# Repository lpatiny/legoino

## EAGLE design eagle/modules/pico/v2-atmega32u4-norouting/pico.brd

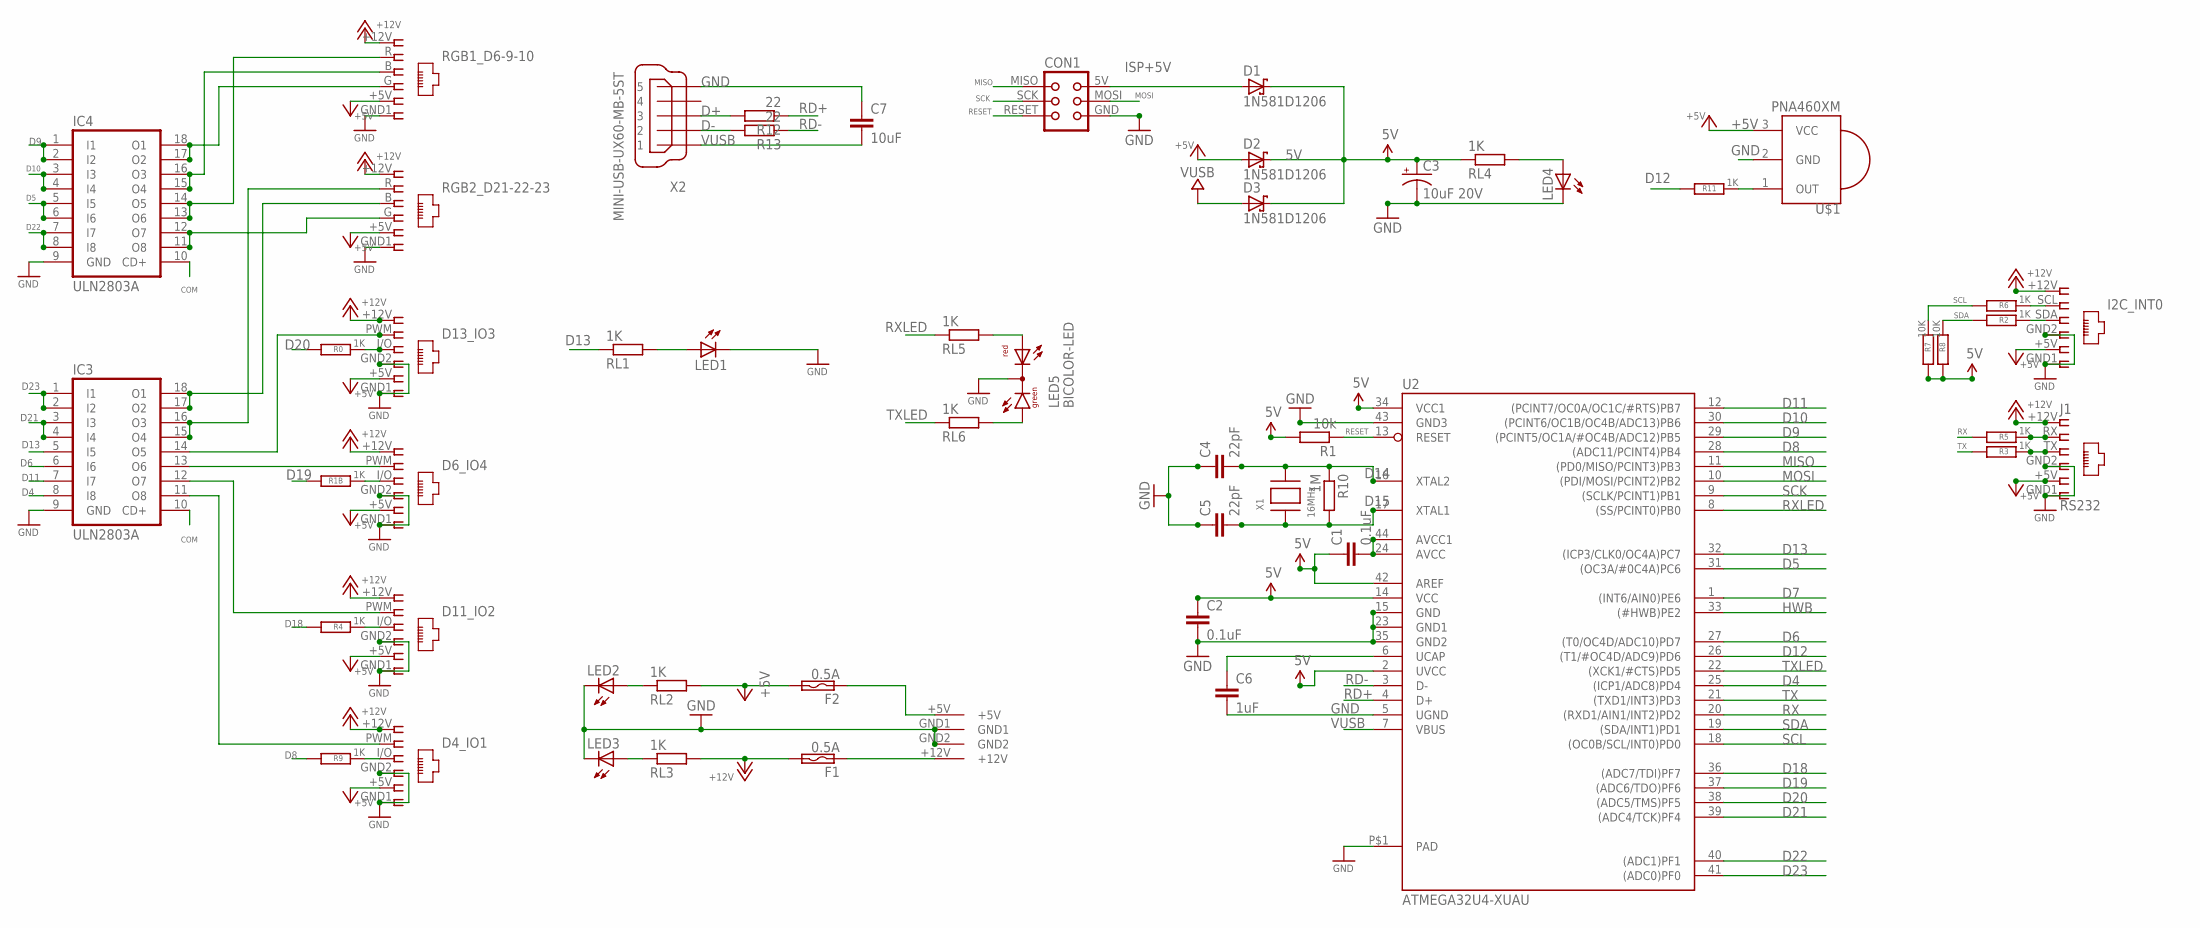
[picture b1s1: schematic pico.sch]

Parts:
C1, C2: 0.1uF; C1206
C3: 10uF 20V; EIA3216-KIT
C4, C5: 22pF; C1206
C6: 1uF; C1206
C7: 10uF; C1206
CON1: TINYISPT; TC2030-MCP-NL
D1, D2, D3: 1N581D1206; LED-1206
D4_IO1: IO1; RJ12-STRAIGHT
D6_IO4: IO3; RJ12-STRAIGHT
D11_IO2: IO2; RJ12-STRAIGHT
D13_IO3: IO4; RJ12-STRAIGHT
F1, F2: 0.5A; C1812
I2C_INT0: I2C; RJ12-STRAIGHT-I2C
IC3, IC4: ULN2803A; SO18W
J1: RS232; RJ12-STRAIGHT-RS232
LED1: LED3MM
LED2: 5V; LED3MM
LED3: 12V; LED3MM
LED4: 5V uC; LED3MM
LED5: BICOLOR-LED; BICOLOR-3MM
R0, R1B, R2, R3, R4, R5, R6, R9, R11: 1K; M1206
R1: 10k; M1206
R7, R8: 10K; M1206
R10: 1M; M1206
R12, R13: 22; M1206
RGB1_D6-9-10: RGB1; RJ12-STRAIGHT-RGB
RGB2_D21-22-23: RGB2; RJ12-STRAIGHT-RGB
RL1, RL2, RL3, RL4, RL5, RL6: 1K; M1206
U2: ATMEGA32U4-XUAU; TQFP44-PAD
U$1: PNA460XM
U$2: KPJX-4S-S
X1: 16MHz; NX6035
X2: MINI-USB-UX60-MB-5ST; UX60-MB-5ST

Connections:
5V: C1.1, C2.1, C3.A (+), D1.C, D2.C, D3.C, R1.2, R7.2, R8.2, RL4.1, U2.2 (UVCC), U2.14 (VCC), U2.34 (VCC1), U2.42 (AREF)
+5V: D2.A, D4_IO1.+5V (5), D6_IO4.+5V (5), D11_IO2.+5V (5), D13_IO3.+5V (5), F2.2, I2C_INT0.+5V (5), J1.+5V (5), RGB1_D6-9-10.+5V (5), RGB2_D21-22-23.+5V (5), RL2.2, U$1.3 (VCC)
+12V: D4_IO1.+12V (1), D6_IO4.+12V (1), D11_IO2.+12V (1), D13_IO3.+12V (1), F1.2, I2C_INT0.+12V (1), J1.+12V (1), RGB1_D6-9-10.+12V (1), RGB2_D21-22-23.+12V (1), RL3.2
COM: IC3.10 (CD+), IC4.10 (CD+)
D2B: D11_IO2.I/O (3), R4.1
D2B1: D4_IO1.I/O (3), R9.1
D2B4: I2C_INT0.SDA (3), R2.1
D2B5: J1.TX (3), R3.1
D2B6: D13_IO3.I/O (3), R0.1
D2B7: D6_IO4.I/O (3), R1B.1
D4: IC3.8 (I8), U2.25 ((ICP1/ADC8)PD4)
D5: IC4.5 (I5), IC4.6 (I6), U2.31 ((OC3A/#0C4A)PC6)
D6: IC3.6 (I6), U2.27 ((T0/OC4D/ADC10)PD7)
D7: U2.1 ((INT6/AIN0)PE6)
D8: R9.2, U2.28 ((ADC11/PCINT4)PB4)
D9: IC4.1 (I1), IC4.2 (I2), U2.29 ((PCINT5/OC1A/#OC4B/ADC12)PB5)
D10: IC4.3 (I3), IC4.4 (I4), U2.30 ((PCINT6/OC1B/OC4B/ADC13)PB6)
D11: IC3.7 (I7), U2.12 ((PCINT7/OC0A/OC1C/#RTS)PB7)
D12: R11.2, U2.26 ((T1/#OC4D/ADC9)PD6)
D13: IC3.5 (I5), RL1.1, U2.32 ((ICP3/CLK0/OC4A)PC7)
D14: C4.2, R10.1, U2.16 (XTAL2), X1.P$2
D15: C5.2, R10.2, U2.17 (XTAL1), X1.P$1
D18: R4.2, U2.36 ((ADC7/TDI)PF7)
D19: R1B.2, U2.37 ((ADC6/TDO)PF6)
D20: R0.2, U2.38 ((ADC5/TMS)PF5)
D21: IC3.3 (I3), IC3.4 (I4), U2.39 ((ADC4/TCK)PF4)
D22: IC4.7 (I7), IC4.8 (I8), U2.40 ((ADC1)PF1)
D23: IC3.1 (I1), IC3.2 (I2), U2.41 ((ADC0)PF0)
D+: R12.2, X2.3
D-: R13.2, X2.2
GND: C2.2, C3.C (-), C4.1, C5.1, C6.2, C7.1, CON1.GND, D4_IO1.GND1 (6), D4_IO1.GND2 (4), D6_IO4.GND1 (6), D6_IO4.GND2 (4), D11_IO2.GND1 (6), D11_IO2.GND2 (4), D13_IO3.GND1 (6), D13_IO3.GND2 (4), I2C_INT0.GND1 (6), I2C_INT0.GND2 (4), IC3.9 (GND), IC4.9 (GND), J1.GND1 (6), J1.GND2 (4), LED1.K (C), LED2.K (C), LED3.K (C), LED4.K (C), LED5.2 (C), RGB1_D6-9-10.GND1 (6), RGB2_D21-22-23.GND1 (6), U2.5 (UGND), U2.15 (GND), U2.23 (GND1), U2.35 (GND2), U2.43 (GND3), U2.P$1 (PAD), U$1.2 (GND), U$2.GND1, U$2.GND2, X2.5
HWB: U2.33 ((#HWB)PE2)
ISP+5V: CON1.5V (VCC), D1.A
MISO: CON1.MISO, U2.11 ((PD0/MISO/PCINT3)PB3)
MOSI: CON1.MOSI, U2.10 ((PDI/MOSI/PCINT2)PB2)
unnamed: IC4.17 (O2), IC4.18 (O1), RGB1_D6-9-10.G (4)
unnamed: D6_IO4.PWM (2), IC3.13 (O6)
unnamed: LED1.A, RL1.2
unnamed: C6.1, U2.6 (UCAP)
unnamed: F2.1, U$2.+5V
unnamed: LED4.A, RL4.2
unnamed: F1.1, U$2.+12V
unnamed: R11.1, U$1.1 (OUT)
unnamed: C1.2, U2.24 (AVCC), U2.44 (AVCC1)
unnamed: LED5.3 (AR), RL5.2
unnamed: LED5.1 (AG), RL6.2
unnamed: IC3.15 (O4), IC3.16 (O3), RGB2_D21-22-23.R (2)
unnamed: D11_IO2.PWM (2), IC3.12 (O7)
unnamed: IC3.17 (O2), IC3.18 (O1), RGB2_D21-22-23.B (3)
unnamed: IC4.15 (O4), IC4.16 (O3), RGB1_D6-9-10.B (3)
unnamed: D4_IO1.PWM (2), IC3.11 (O8)
unnamed: IC4.11 (O8), IC4.12 (O7), RGB2_D21-22-23.G (4)
unnamed: D13_IO3.PWM (2), IC3.14 (O5)
unnamed: IC4.13 (O6), IC4.14 (O5), RGB1_D6-9-10.R (2)
unnamed: J1.RX (2), R5.1
unnamed: I2C_INT0.SCL (2), R6.1
unnamed: LED3.A, RL3.1
unnamed: LED2.A, RL2.1
RD+: R12.1, U2.4 (D+)
RD-: R13.1, U2.3 (D-)
RESET: CON1.RESET, R1.1, U2.13 (RESET)
RX: R5.2, U2.20 ((RXD1/AIN1/INT2)PD2)
RXLED: RL5.1, U2.8 ((SS/PCINT0)PB0)
SCK: CON1.SCK, U2.9 ((SCLK/PCINT1)PB1)
SCL: R6.2, R7.1, U2.18 ((OC0B/SCL/INT0)PD0)
SDA: R2.2, R8.1, U2.19 ((SDA/INT1)PD1)
TX: R3.2, U2.21 ((TXD1/INT3)PD3)
TXLED: RL6.1, U2.22 ((XCK1/#CTS)PD5)
VUSB: C7.2, D3.A, U2.7 (VBUS), X2.1

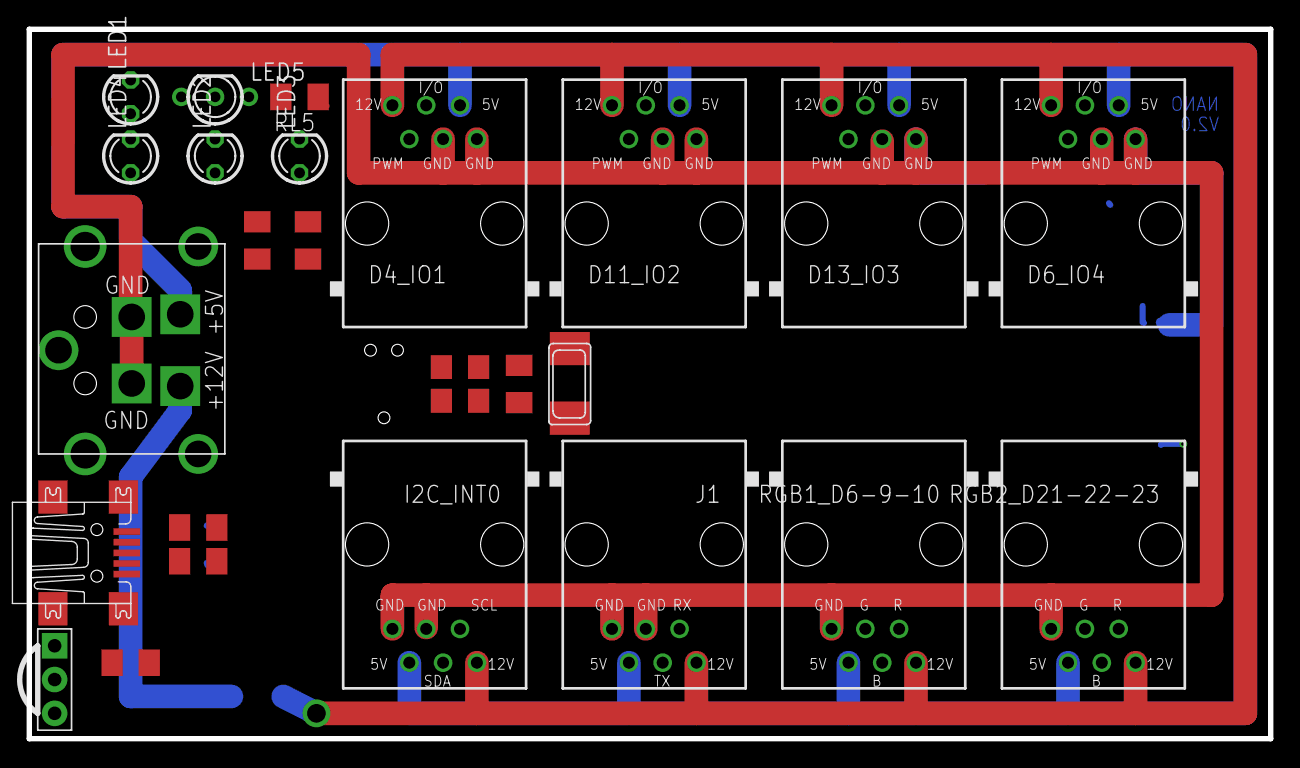
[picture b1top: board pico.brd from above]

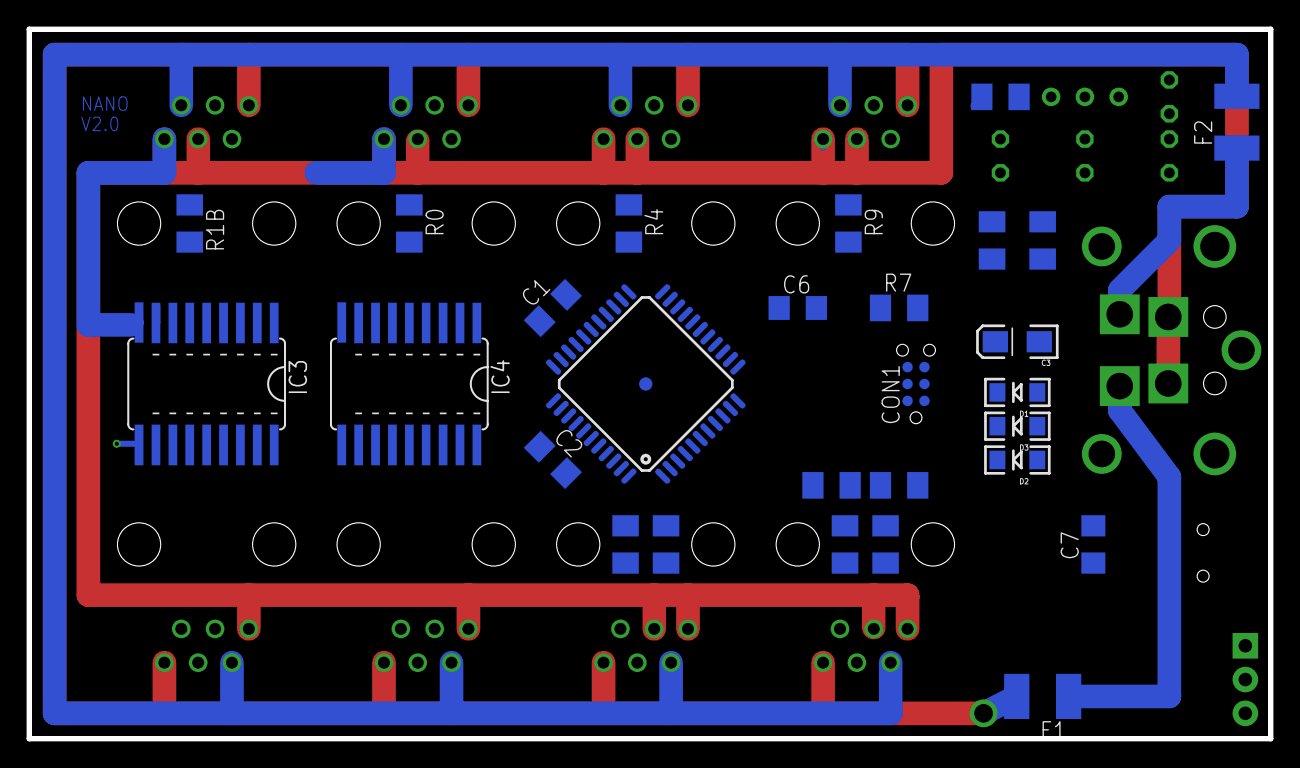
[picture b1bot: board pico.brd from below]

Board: 2 copper layers, 93.3 x 53.3 mm, 54 parts (28 on the bottom side), 67 nets.

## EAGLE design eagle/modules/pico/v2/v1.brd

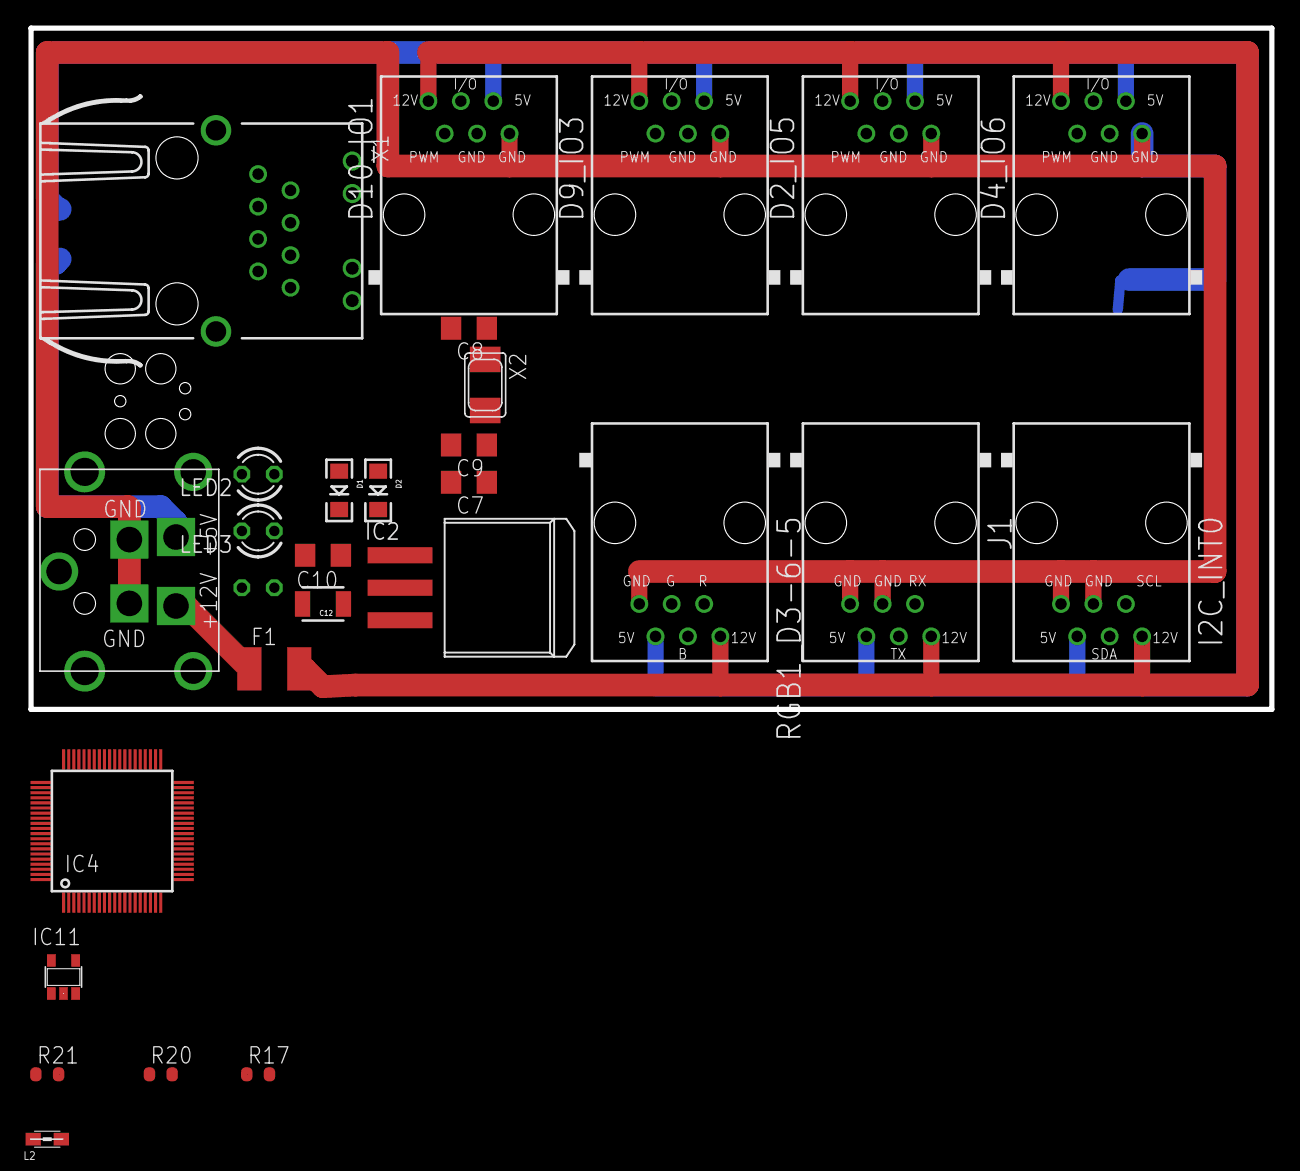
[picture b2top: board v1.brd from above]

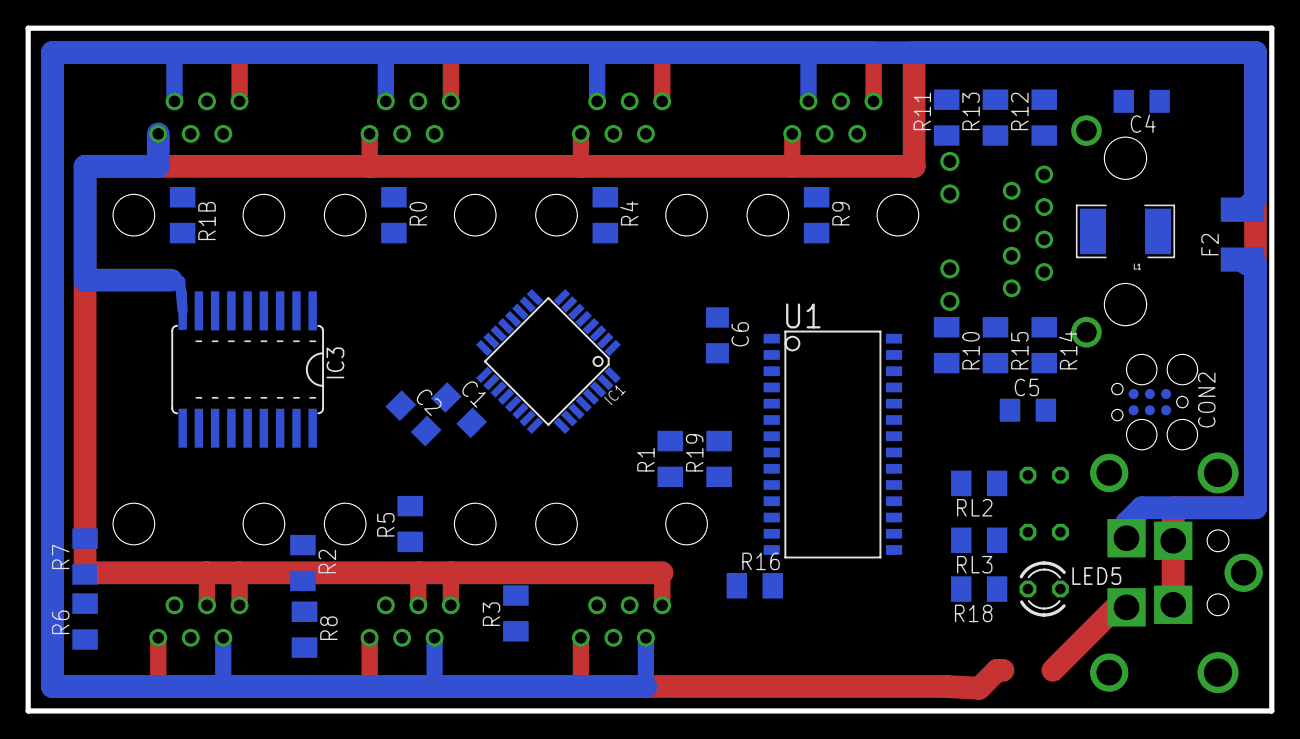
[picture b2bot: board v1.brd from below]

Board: 2 copper layers, 97.2 x 53.3 mm, 61 parts (34 on the bottom side), 71 nets.

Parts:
C1, C2: 0.1uF; C1206
C4, C5: 10nF; C1206
C6: 10uF; C1206
C7: 100nF; C1206
C8, C9: 18pF; C1206
C10: 470nF; C1206
C12: 33uF; 1210
CON2: TC2030-MCP
D1, D2: 1N581D1206; LED-1206
D2_IO5: IO5; RJ12-STRAIGHT
D4_IO6: IO6; RJ12-STRAIGHT
D9_IO3: IO3; RJ12-STRAIGHT
D10_IO1: IO1; RJ12-STRAIGHT
F1, F2: POLYSWITCHSMD1812; C1812
I2C_INT0: I2C; RJ12-STRAIGHT-I2C
IC1: MEGA8-AI; TQFP32-08
IC2: LM3940IS-3.3F; DD-3
IC3: ULN2803A; SO18W
IC4: W5100; SQFP-S-10X10-80
IC11: 74LVC1G14DBV; SOT23-5
J1: RJ12STRAIGHT-RS232-SERVER; RJ12-STRAIGHT-RS232
L1: 10uH; INDUCTOR-1206
L2: BLM21; 0805
LED2, LED3, LED5: LED3MM
R0, R1B, R2, R3, R4, R5, R6, R9, R18: 1K; M1206
R1: 10k; M1206
R7, R8: 10K; M1206
R10, R11: 470; M1206
R12, R13, R14, R15: 50; M1206
R16: 2k; M1206
R17: 10k; R0603-ROUND
R19: 100k; M1206
R20: 12k 1%; R0603-ROUND
R21: 300R 1%; R0603-ROUND
RGB1_D3-6-5: RGB1; RJ12-STRAIGHT-RGB
RL2, RL3: 1K; M1206
U1: SO28W
U$2: KPJX-4S-S
X1: hy911103a; J1
X2: NX5032

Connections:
3.3V: C7.1, U1.15, U1.19, U1.20, U1.28
5V: R7.2, R8.2
+1V8: IC4.11, IC4.15, IC4.16, IC4.33, IC4.69, L2.1
+1V8A: IC4.7, IC4.74, L2.2
+3V3: C1.1, C2.1, C12.1, IC1.4, IC1.6, IC1.18, IC2.3, IC4.12, IC4.18, IC4.44, L1.P$1, R1.2, R17.1, R18.2, R19.2, U1.25
+5V: D2.A, D2_IO5.+5V, D4_IO6.+5V, D9_IO3.+5V, D10_IO1.+5V, F2.2, I2C_INT0.+5V, J1.+5V, RGB1_D3-6-5.+5V, RL2.2
+12V: D2_IO5.+12V, D4_IO6.+12V, D9_IO3.+12V, D10_IO1.+12V, F1.2, I2C_INT0.+12V, J1.+12V, RGB1_D3-6-5.+12V, RL3.2
A0: IC1.23, R0.2
A1: IC1.24, R1B.2
A2: IC1.25, R4.2
A3: IC1.26, R9.2
D2: IC1.32, IC3.5
D2B: D9_IO3.I/O, R4.1
D2B1: D10_IO1.I/O, R9.1
D2B4: I2C_INT0.SDA, R2.1
D2B5: J1.TX, R3.1
D2B6: D2_IO5.I/O, R0.1
D2B7: D4_IO6.I/O, R1B.1
D3: IC1.1, IC3.1
D4: IC1.2, IC3.6
D5: IC1.9, IC3.3
D6: IC1.10, IC3.2
D7: IC1.11, IC3.8
D8: IC1.12, IC3.4
D9: IC1.13, IC3.7
D10: IC1.14, R19.1, U1.9
GND: C2.2, C4.1, C5.1, C6.2, C7.2, C8.2, C9.2, C10.2, C12.2, CON2.GND, D2_IO5.GND1, D2_IO5.GND2, D4_IO6.GND1, D4_IO6.GND2, D9_IO3.GND1, D9_IO3.GND2, D10_IO1.GND1, D10_IO1.GND2, I2C_INT0.GND1, I2C_INT0.GND2, IC1.3, IC1.5, IC1.21, IC2.2, IC3.9, IC4.4, IC4.10, IC4.13, IC4.14, IC4.17, IC4.19, IC4.20, IC4.21, IC4.22, IC4.23, IC4.24, IC4.25, IC4.26, IC4.32, IC4.34, IC4.35, IC4.36, IC4.37, IC4.38, IC4.39, IC4.40, IC4.41, IC4.42, IC4.43, IC4.45, IC4.46, IC4.47, IC4.48, IC4.49, IC4.50, IC4.51, IC4.52, IC4.53, IC4.54, IC4.63, IC4.64, IC4.65, IC4.68, IC4.77, IC11.3, J1.GND1, J1.GND2, LED2.K, LED3.K, LED5.K, R16.1, R21.2, RGB1_D3-6-5.GND1, U1.2, U1.11, U1.18, U1.21, U1.22, U$2.GND1, U$2.GND2, X1.10, X1.11
ISP+5V: CON2.5V, D1.A
MISO: CON2.MISO, IC1.16, IC4.27, U1.6
MOSI: CON2.MOSI, IC1.15, IC4.28, U1.7
unnamed: IC3.16, RGB1_D3-6-5.G
unnamed: D4_IO6.PWM, IC3.13
unnamed: C1.2, IC1.20
unnamed: LED5.A, R18.1
unnamed: F2.1, U$2.+5V
unnamed: F1.1, U$2.+12V
unnamed: R10.2, U1.27
unnamed: R11.2, U1.26
unnamed: R10.1, X1.9
unnamed: R11.1, X1.12
unnamed: R15.1, U1.17, X1.1
unnamed: R14.1, U1.16, X1.2
unnamed: R13.1, U1.13, X1.7
unnamed: R12.1, U1.12, X1.8
unnamed: C4.2, L1.P$2, R12.2, R13.2, X1.3
unnamed: C5.2, R14.2, R15.2
unnamed: C10.1, D1.C, D2.C, IC2.1
unnamed: D9_IO3.PWM, IC3.12
unnamed: C6.1, U1.1
unnamed: R16.2, U1.14
unnamed: C9.1, U1.23, X2.P$1
unnamed: C8.1, U1.24, X2.P$2
unnamed: R20.2, R21.1
unnamed: IC4.1, R20.1
unnamed: IC4.55, IC4.57, IC4.58
unnamed: IC3.17, RGB1_D3-6-5.B
unnamed: D10_IO1.PWM, IC3.11
unnamed: D2_IO5.PWM, IC3.14
unnamed: IC3.18, RGB1_D3-6-5.R
unnamed: J1.RX, R5.1
unnamed: I2C_INT0.SCL, R6.1
unnamed: LED3.A, RL3.1
unnamed: LED2.A, RL2.1
RESET: CON2.RESET, IC1.29, R1.1, U1.10
RX: IC1.30, R5.2
SCK: CON2.SCK, IC1.17, IC4.30, U1.8
SCL: IC1.28, R6.2, R7.1
SDA: IC1.27, R2.2, R8.1
SEN: IC4.31, IC11.4, R17.2
SS: IC4.29, IC11.2
TX: IC1.31, R3.2

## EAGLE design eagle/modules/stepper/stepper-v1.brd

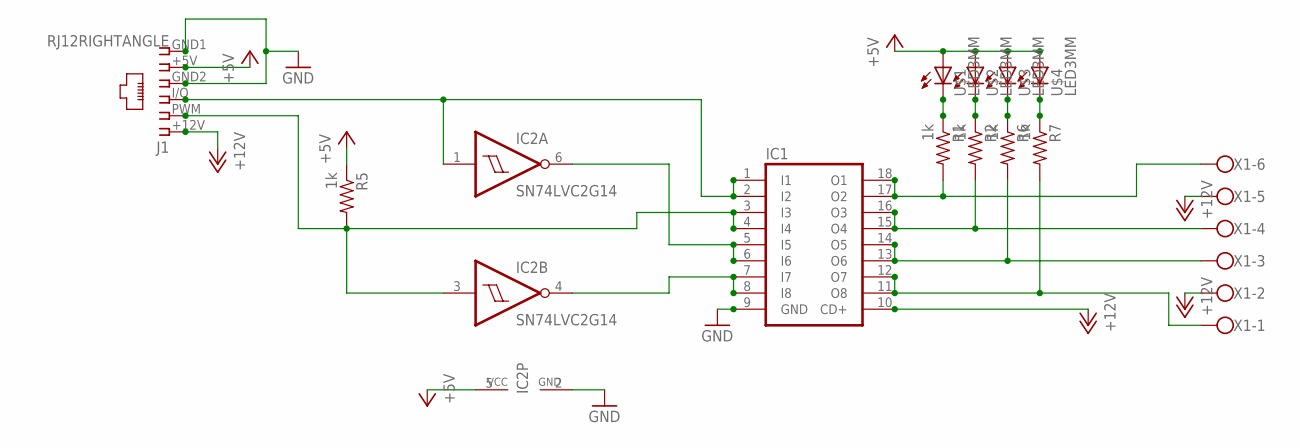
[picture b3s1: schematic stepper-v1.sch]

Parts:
IC1: ULN2803A; SO18W
IC2: SN74LVC2G14; SOT23-6
J1: RJ12RIGHTANGLE; RJ12-RIGHTANGLE
R1, R2, R5, R6, R7: 1k; 1206
U$1, U$2, U$3, U$4: LED3MM
X1: W237-6

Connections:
+5V: IC2.5 (VCC), J1.+5V (5), R5.1, U$1.A, U$2.A, U$3.A, U$4.A
+12V: IC1.10 (CD+), J1.+12V (1), X1.2, X1.5
GND: IC1.9 (GND), IC2.2 (GND), J1.GND1 (6), J1.GND2 (4)
unnamed: IC1.1 (I1), IC1.2 (I2), IC2.1 (I), J1.I/O (3)
unnamed: IC1.3 (I3), IC1.4 (I4), IC2.3 (I), J1.PWM (2), R5.2
unnamed: IC1.17 (O2), IC1.18 (O1), R1.2, X1.6
unnamed: IC1.15 (O4), IC1.16 (O3), R2.2, X1.4
unnamed: IC1.13 (O6), IC1.14 (O5), R6.2, X1.3
unnamed: IC1.11 (O8), IC1.12 (O7), R7.2, X1.1
unnamed: IC1.7 (I7), IC1.8 (I8), IC2.4 (O)
unnamed: R1.1, U$1.K (C)
unnamed: R2.1, U$2.K (C)
unnamed: R6.1, U$3.K (C)
unnamed: R7.1, U$4.K (C)
unnamed: IC1.5 (I5), IC1.6 (I6), IC2.6 (O)

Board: 2 copper layers, 13 parts (2 on the bottom side), 15 nets, no tracks yet.

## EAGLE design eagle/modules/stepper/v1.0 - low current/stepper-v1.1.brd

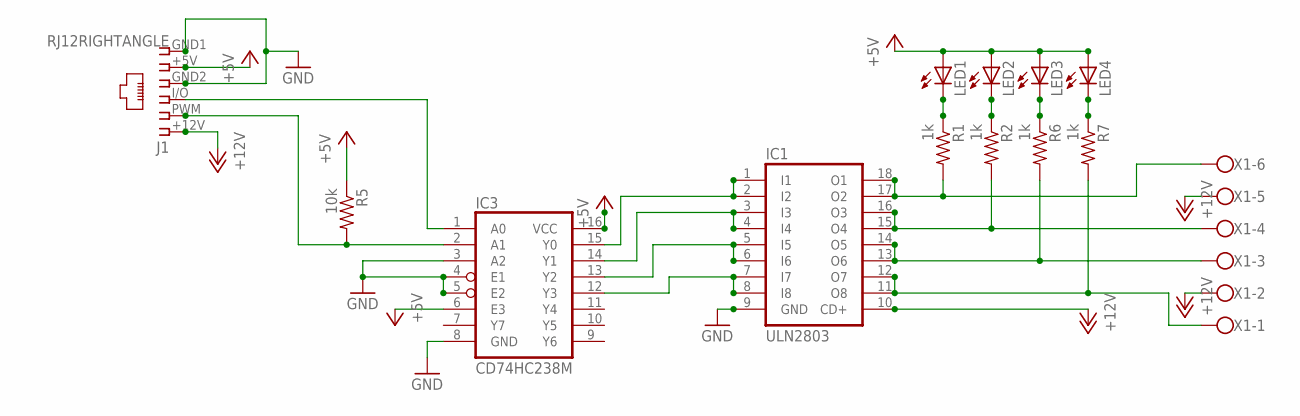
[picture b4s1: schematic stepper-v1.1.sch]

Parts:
IC1: ULN2803; SO18W
IC3: CD74HC238M; SO16
J1: RJ12RIGHTANGLE; RJ12-RIGHTANGLE
LED1, LED2, LED3, LED4: LED3MM
R1, R2, R6, R7: 1k; 1206
R5: 10k; 1206
X1: W237-6

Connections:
+5V: IC3.6 (E3), IC3.16 (VCC), J1.+5V (5), LED1.A, LED2.A, LED3.A, LED4.A, R5.1
+12V: IC1.10 (CD+), J1.+12V (1), X1.2, X1.5
GND: IC1.9 (GND), IC3.3 (A2), IC3.4 (E1), IC3.5 (E2), IC3.8 (GND), J1.GND1 (6), J1.GND2 (4)
unnamed: IC1.1 (I1), IC1.2 (I2), IC3.15 (Y0)
unnamed: IC3.2 (A1), J1.PWM (2), R5.2
unnamed: IC1.17 (O2), IC1.18 (O1), R1.2, X1.6
unnamed: IC1.15 (O4), IC1.16 (O3), R2.2, X1.4
unnamed: IC1.13 (O6), IC1.14 (O5), R6.2, X1.3
unnamed: IC1.11 (O8), IC1.12 (O7), R7.2, X1.1
unnamed: IC1.7 (I7), IC1.8 (I8), IC3.12 (Y3)
unnamed: IC1.3 (I3), IC1.4 (I4), IC3.14 (Y1)
unnamed: LED1.K (C), R1.1
unnamed: LED2.K (C), R2.1
unnamed: LED3.K (C), R6.1
unnamed: LED4.K (C), R7.1
unnamed: IC3.1 (A0), J1.I/O (3)
unnamed: IC1.5 (I5), IC1.6 (I6), IC3.13 (Y2)

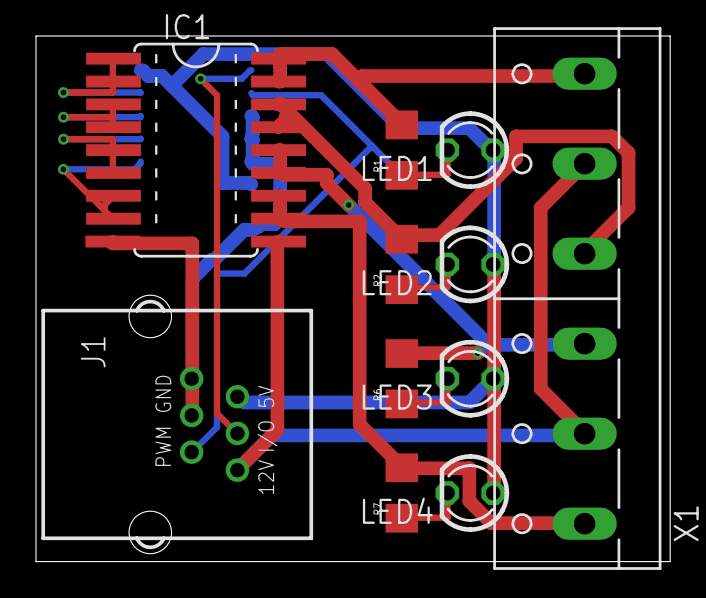
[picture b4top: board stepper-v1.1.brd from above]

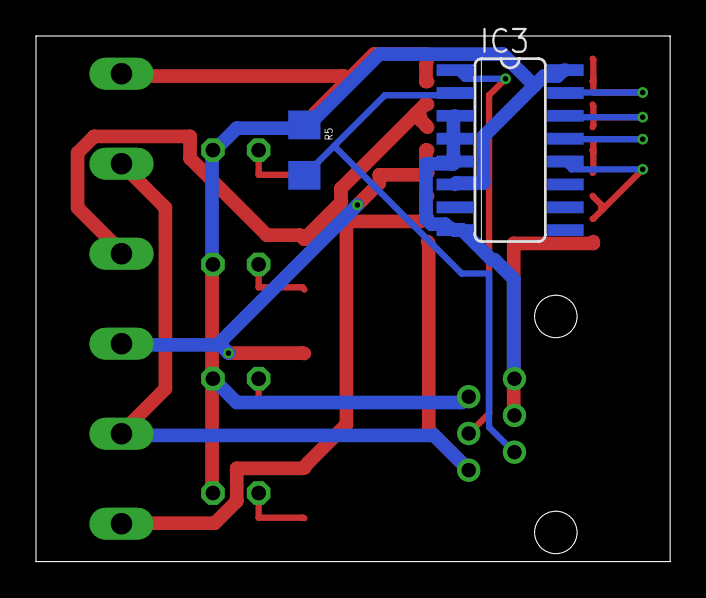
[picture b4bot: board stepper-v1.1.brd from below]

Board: 2 copper layers, 35.2 x 29.2 mm, 13 parts (2 on the bottom side), 17 nets.

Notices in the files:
parts and their libraries:
lpatiny: ©2009 ROFA.cz - modified and updated by Robert Darlington ‹rdarlington@gmail.com›
SparkFun: Licensing: CC v3.0 Share-Alike You are welcome to use this library for commercial purposes.
